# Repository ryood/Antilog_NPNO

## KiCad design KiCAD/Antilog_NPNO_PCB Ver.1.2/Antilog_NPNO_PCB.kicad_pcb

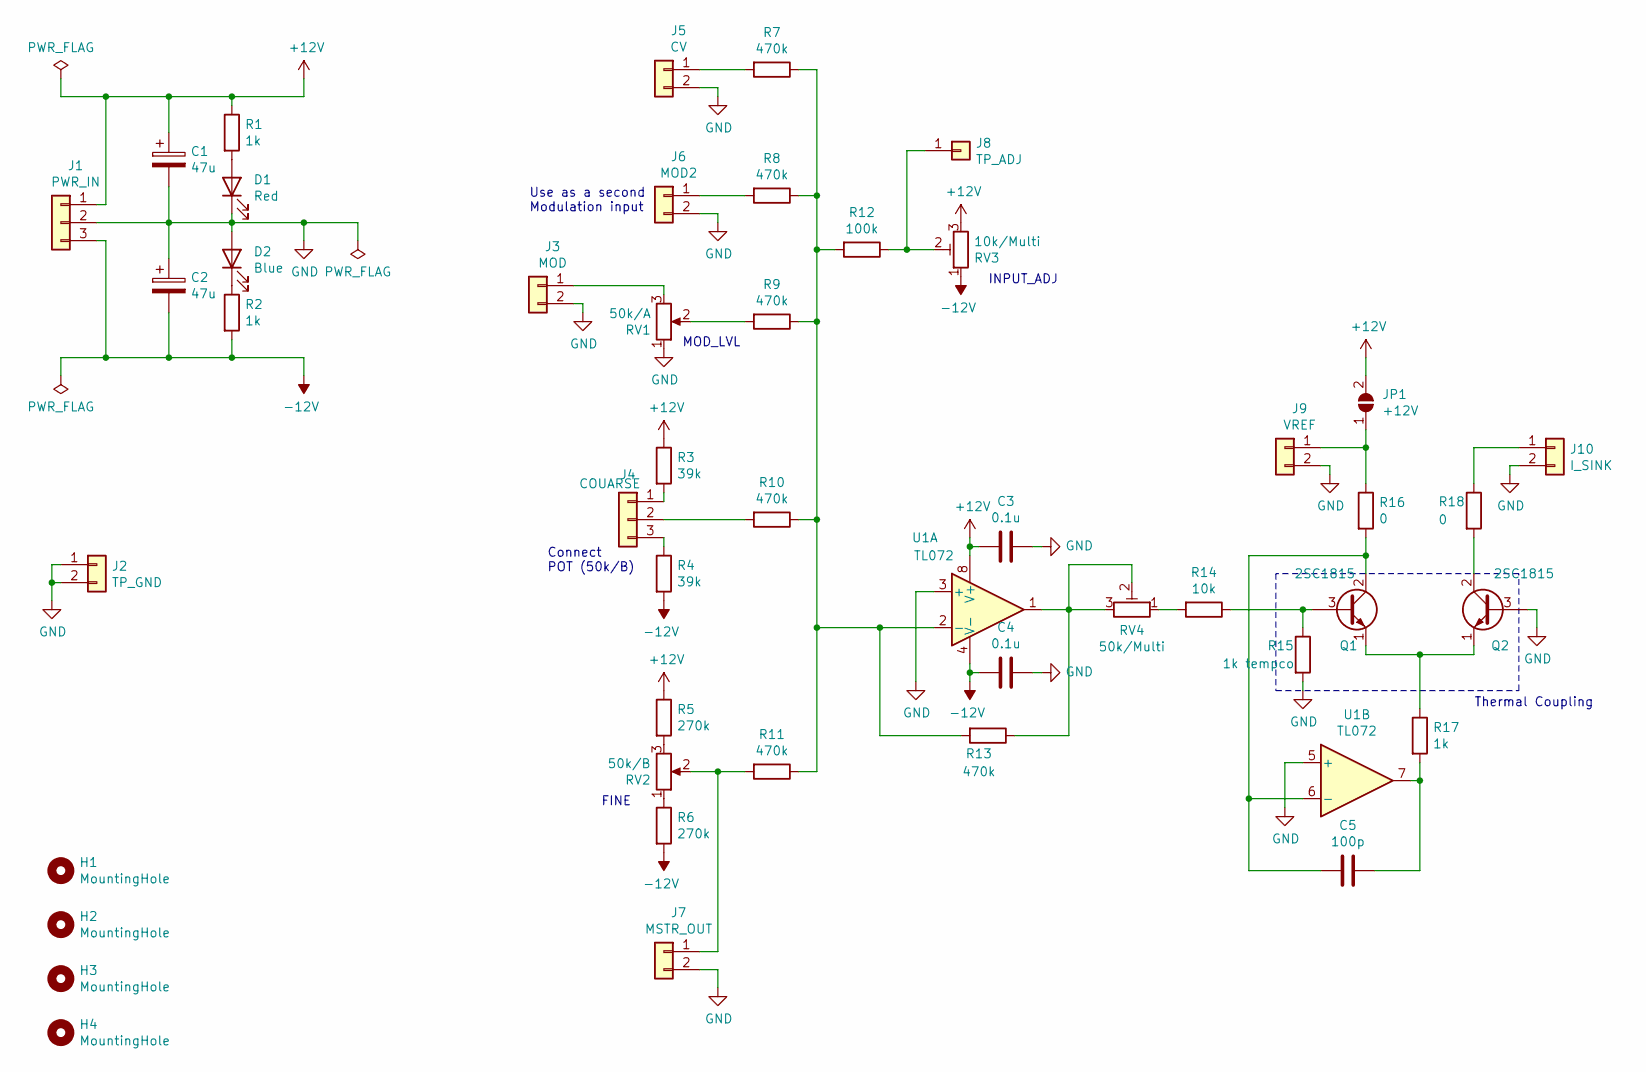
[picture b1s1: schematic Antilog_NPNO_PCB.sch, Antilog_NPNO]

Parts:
C1, C2: 47u; CP_Radial_D6.3mm_P2.50mm
C3, C4: 0.1u; C_Disc_D3.0mm_W1.6mm_P2.50mm
C5: 100p; C_Disc_D5.0mm_W2.5mm_P5.00mm
D1: Red; LED_D3.0mm
D2: Blue; LED_D3.0mm
H1, H2, H3, H4: MountingHole; MountingHole_3.2mm_M3
J1: PWR_IN; JST_XH_S3B-XH-A_1x03_P2.50mm_Horizontal
J2: TP_GND; PinHeader_1x02_P2.54mm_Vertical
J3: MOD; JST_XH_B2B-XH-A_1x02_P2.50mm_Vertical
J4: COUARSE; JST_XH_B3B-XH-A_1x03_P2.50mm_Vertical
J5: CV; JST_XH_B2B-XH-A_1x02_P2.50mm_Vertical
J6: MOD2; JST_XH_B2B-XH-A_1x02_P2.50mm_Vertical
J7: MSTR_OUT; JST_XH_B2B-XH-A_1x02_P2.50mm_Vertical
J8: TP_ADJ; TestPoint_Loop_D1.80mm_Drill1.0mm_Beaded
J9: VREF; JST_XH_S2B-XH-A_1x02_P2.50mm_Horizontal
J10: I_SINK; JST_XH_S2B-XH-A_1x02_P2.50mm_Horizontal
JP1: +12V; SolderJumper-2_P1.3mm_Open_RoundedPad1.0x1.5mm
Q1, Q2: 2SC1815; TO-92_Wide
R1, R2, R17: 1k; R_Axial_DIN0207_L6.3mm_D2.5mm_P7.62mm_Horizontal
R3, R4: 39k; R_Axial_DIN0207_L6.3mm_D2.5mm_P7.62mm_Horizontal
R5, R6: 270k; R_Axial_DIN0207_L6.3mm_D2.5mm_P7.62mm_Horizontal
R7, R8, R9, R10, R11, R13: 470k; R_Axial_DIN0207_L6.3mm_D2.5mm_P7.62mm_Horizontal
R12: 100k; R_Axial_DIN0207_L6.3mm_D2.5mm_P7.62mm_Horizontal
R14: 10k; R_Axial_DIN0207_L6.3mm_D2.5mm_P7.62mm_Horizontal
R15: 1k tempco; R_Axial_DIN0207_L6.3mm_D2.5mm_P7.62mm_Horizontal
R16, R18: 0; R_Axial_DIN0207_L6.3mm_D2.5mm_P7.62mm_Horizontal
RV1: 50k/A; Potentiometer_Alps_RK097_Single_Horizontal
RV2: 50k/B; Potentiometer_Alps_RK097_Single_Horizontal
RV3: 10k/Multi; Potentiometer_Bourns_3006P_Horizontal
RV4: 50k/Multi; Potentiometer_Bourns_3006P_Horizontal
U1: TL072; DIP-8_W7.62mm_Socket

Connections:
+12V: C1.1, C3.2, J1.1, JP1.2 (B), R1.1, R3.1, R5.1, RV3.3, U1.8 (V+)
-12V: C2.2, C4.2, J1.3, R2.2, R4.2, R6.2, RV3.1, U1.4 (V-)
GND: C1.2, C2.1, C3.1, C4.1, D1.1 (K), D2.2 (A), J1.2, J2.1, J2.2, J3.2, J5.2, J6.2, J7.2, J9.2, J10.2, Q2.3 (B), R15.2, RV1.1, U1.3 (+), U1.5 (+)
unnamed: C5.1, R17.2, U1.7
unnamed: C5.2, Q1.2 (C), R16.2, U1.6 (-)
unnamed: D1.2 (A), R1.2
unnamed: D2.1 (K), R2.1
unnamed: J3.1, RV1.3
unnamed: J4.1, R3.2
unnamed: J4.2, R10.2
unnamed: J4.3, R4.1
unnamed: J5.1, R7.2
unnamed: J6.1, R8.2
unnamed: J7.1, R11.2, RV2.2
unnamed: J8.1, R12.1, RV3.2
unnamed: J9.1, JP1.1 (A), R16.1
unnamed: J10.1, R18.1
unnamed: Q1.1 (E), Q2.1 (E), R17.1
unnamed: Q1.3 (B), R14.1, R15.1
unnamed: Q2.2 (C), R18.2
unnamed: R5.2, RV2.3
unnamed: R6.1, RV2.1
unnamed: R9.2, RV1.2
unnamed: R7.1, R8.1, R9.1, R10.1, R11.1, R12.2, R13.2, U1.2 (-)
unnamed: R13.1, RV4.2, RV4.3, U1.1
unnamed: R14.2, RV4.1

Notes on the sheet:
FINE
MOD_LVL
INPUT_ADJ
Thermal Coupling
Use as a second Modulation input
Connect POT (50k/B)

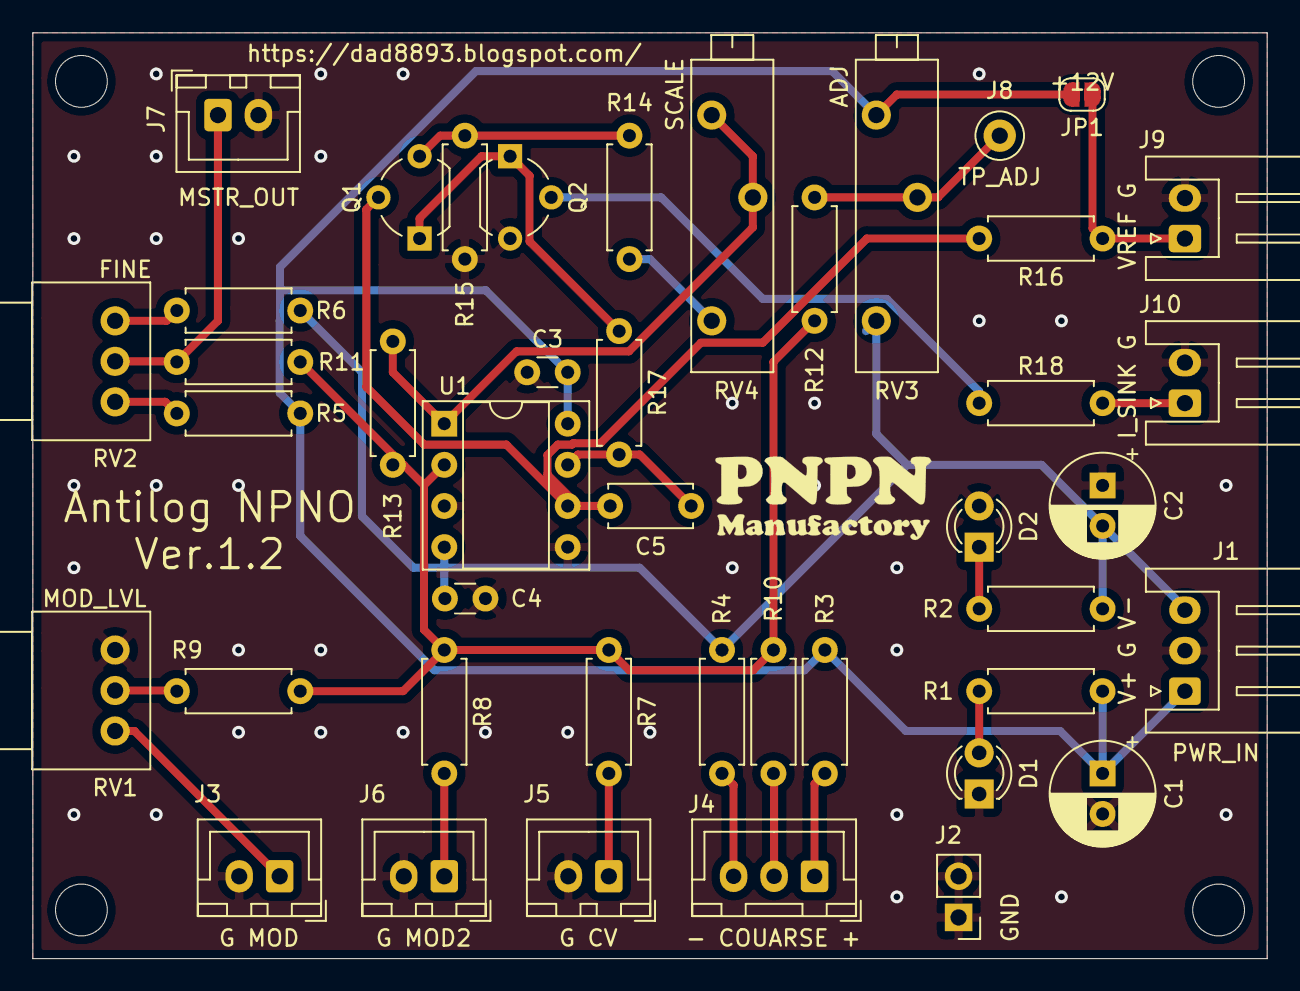
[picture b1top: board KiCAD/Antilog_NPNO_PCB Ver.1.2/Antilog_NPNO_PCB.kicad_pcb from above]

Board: 2 copper layers, 76.2 x 57.2 mm, 47 parts (0 on the bottom side), 26 nets.

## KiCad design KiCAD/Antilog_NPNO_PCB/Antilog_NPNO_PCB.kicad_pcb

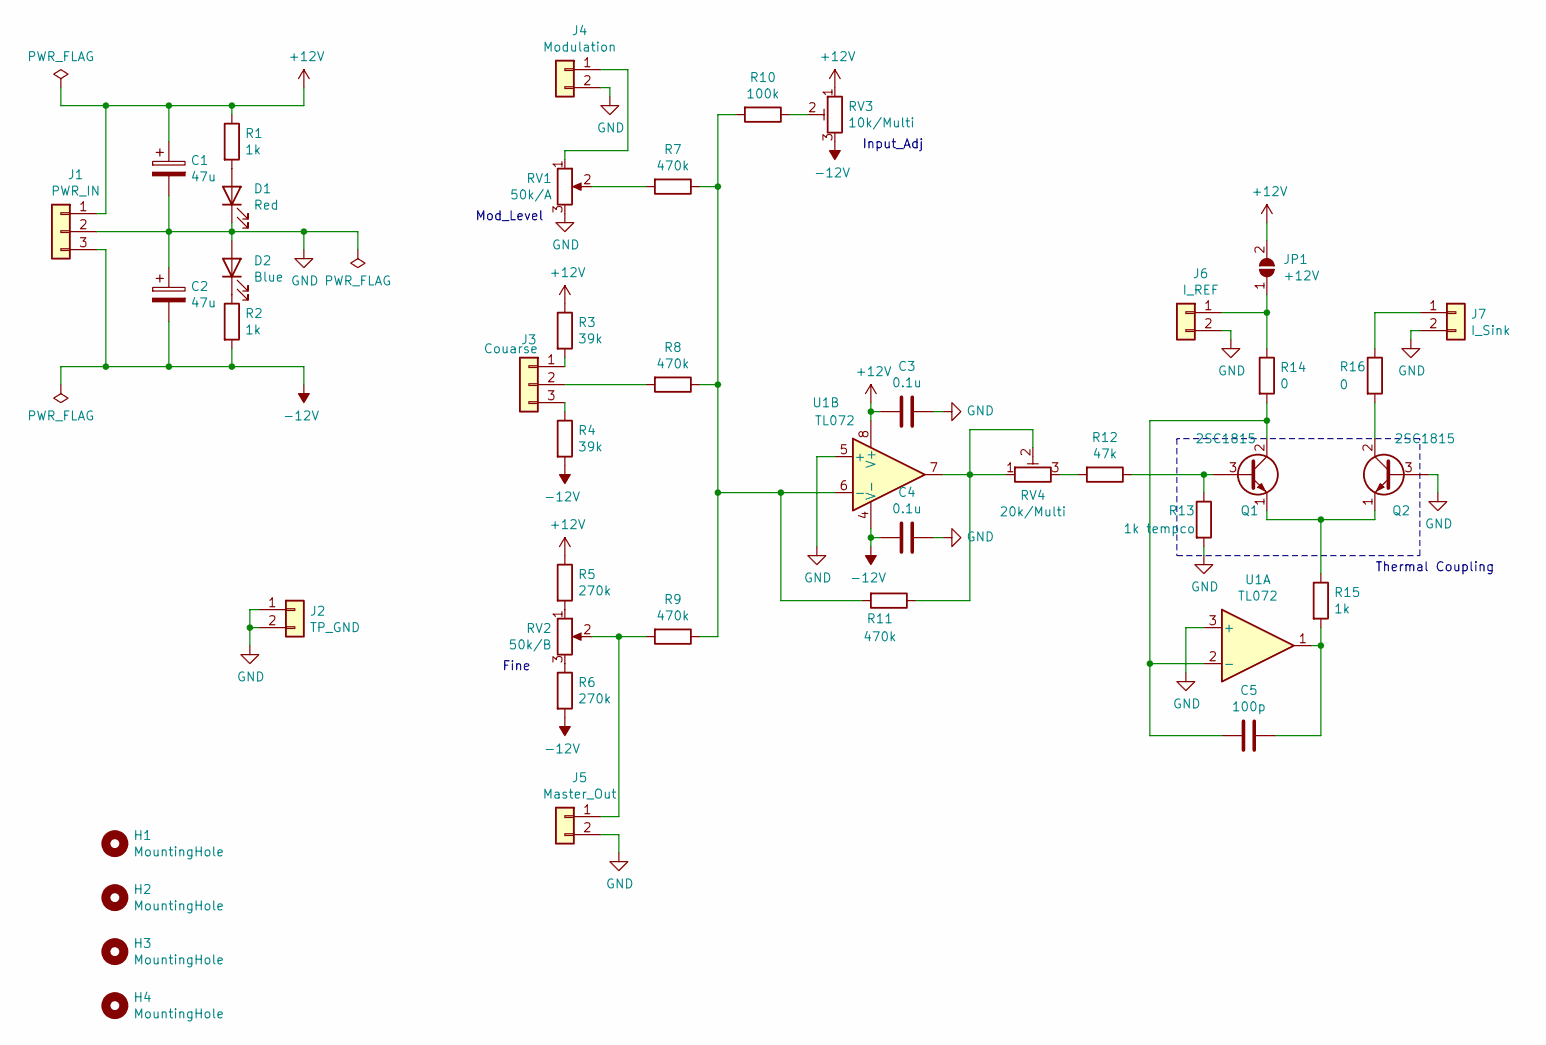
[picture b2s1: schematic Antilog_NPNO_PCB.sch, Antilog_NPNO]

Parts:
C1, C2: 47u; CP_Radial_D6.3mm_P2.50mm
C3, C4: 0.1u; C_Disc_D3.0mm_W1.6mm_P2.50mm
C5: 100p; C_Disc_D5.0mm_W2.5mm_P5.00mm
D1: Red; LED_D3.0mm
D2: Blue; LED_D3.0mm
H1, H2, H3, H4: MountingHole; MountingHole_3.2mm_M3
J1: PWR_IN; JST_XH_B3B-XH-A_1x03_P2.50mm_Vertical
J2: TP_GND; PinHeader_1x02_P2.54mm_Vertical
J3: Couarse; JST_XH_B3B-XH-A_1x03_P2.50mm_Vertical
J4: Modulation; JST_XH_B2B-XH-A_1x02_P2.50mm_Vertical
J5: Master_Out; JST_XH_B2B-XH-A_1x02_P2.50mm_Vertical
J6: I_REF; JST_XH_B2B-XH-A_1x02_P2.50mm_Vertical
J7: I_Sink; JST_XH_B2B-XH-A_1x02_P2.50mm_Vertical
JP1: +12V; SolderJumper-2_P1.3mm_Open_RoundedPad1.0x1.5mm
Q1, Q2: 2SC1815; TO-92_Wide
R1, R2, R15: 1k; R_Axial_DIN0207_L6.3mm_D2.5mm_P7.62mm_Horizontal
R3, R4: 39k; R_Axial_DIN0207_L6.3mm_D2.5mm_P7.62mm_Horizontal
R5, R6: 270k; R_Axial_DIN0207_L6.3mm_D2.5mm_P7.62mm_Horizontal
R7, R8, R9, R11: 470k; R_Axial_DIN0207_L6.3mm_D2.5mm_P7.62mm_Horizontal
R10: 100k; R_Axial_DIN0207_L6.3mm_D2.5mm_P7.62mm_Horizontal
R12: 47k; R_Axial_DIN0207_L6.3mm_D2.5mm_P7.62mm_Horizontal
R13: 1k tempco; R_Axial_DIN0207_L6.3mm_D2.5mm_P7.62mm_Horizontal
R14, R16: 0; R_Axial_DIN0207_L6.3mm_D2.5mm_P7.62mm_Horizontal
RV1: 50k/A; Potentiometer_Alps_RK097_Single_Horizontal
RV2: 50k/B; Potentiometer_Alps_RK097_Single_Horizontal
RV3: 10k/Multi; Potentiometer_Bourns_3296X_Horizontal
RV4: 20k/Multi; Potentiometer_Bourns_3296X_Horizontal
U1: TL072; DIP-8_W7.62mm_Socket

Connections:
+12V: C1.1, C3.2, J1.1, JP1.2 (B), R1.1, R3.1, R5.1, RV3.1, U1.8 (V+)
-12V: C2.2, C4.2, J1.3, R2.2, R4.2, R6.2, RV3.3, U1.4 (V-)
GND: C1.2, C2.1, C3.1, C4.1, D1.1 (K), D2.2 (A), J1.2, J2.1, J2.2, J4.2, J5.2, J6.2, J7.2, Q2.3 (B), R13.2, RV1.3, U1.3 (+), U1.5 (+)
unnamed: C5.1, R15.2, U1.1
unnamed: C5.2, Q1.2 (C), R14.2, U1.2 (-)
unnamed: D1.2 (A), R1.2
unnamed: D2.1 (K), R2.1
unnamed: J3.1, R3.2
unnamed: J3.2, R8.2
unnamed: J3.3, R4.1
unnamed: J4.1, RV1.1
unnamed: J5.1, R9.2, RV2.2
unnamed: J6.1, JP1.1 (A), R14.1
unnamed: J7.1, R16.1
unnamed: Q1.1 (E), Q2.1 (E), R15.1
unnamed: Q1.3 (B), R12.1, R13.1
unnamed: Q2.2 (C), R16.2
unnamed: R5.2, RV2.1
unnamed: R6.1, RV2.3
unnamed: R7.2, RV1.2
unnamed: R10.1, RV3.2
unnamed: R7.1, R8.1, R9.1, R10.2, R11.2, U1.6 (-)
unnamed: R11.1, RV4.1, RV4.2, U1.7
unnamed: R12.2, RV4.3

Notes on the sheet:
Fine
Mod_Level
Input_Adj
Thermal Coupling

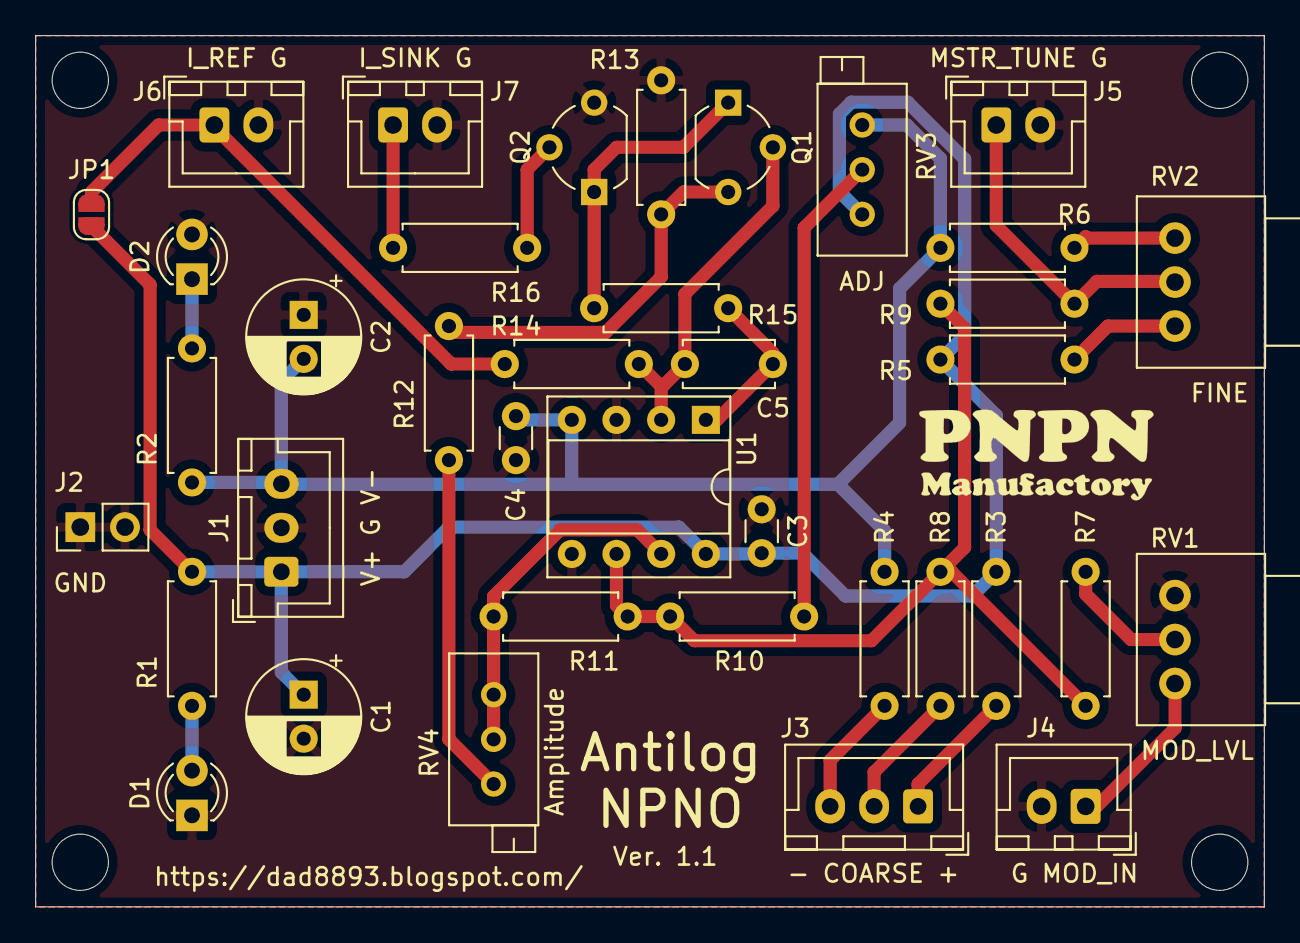
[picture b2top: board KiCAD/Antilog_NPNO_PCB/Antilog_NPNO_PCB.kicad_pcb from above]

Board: 2 copper layers, 69.8 x 49.5 mm, 42 parts (0 on the bottom side), 24 nets.

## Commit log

2020-11-30 implementation Test
2020-12-29 PCB Design
2020-12-29 Updated: Ver.1.2 PCB Design
